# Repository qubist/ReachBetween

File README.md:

RB02
====

Simple, cheap, hackable, DIY, open-source USB-C input switcher

Background
----------

I couldn't find a good USB-C switch with two outputs that wasn't hundreds of
dollars, so I built my own. (Also I wanted an excuse to learn PCB design, and I
was able to secure a few free sample rotary switches from an electronics
company.) The result is the RB02, a two-output one-input bidirectional USB-C
input switcher smaller than a credit card.

The RB02 has three USB-C ports, one on the front and two on the back. A knob on top has three positions, left, right, and center. In the left or right position, the device connects the USB port on the front to the left or right USB port on the back. 

It's resonable to make as a weekend project as long as you've got a fine
soldering iron for the few surface-mount pads.

Gallery
-------

FIXME

Bill of Materials
-----------------

| Item                                              | Manufacturer  | Part number      | Quantity | Unit price | Total price              |
|---------------------------------------------------|---------------|------------------|----------|------------|--------------------------|
| Rotary switch                                     | NKK Switches  | MRA-403-A        | 1        | $24.17     | $24.17                   |
| 18-8 Stainless Steel Socket Head Screw, M2 x 25mm | McMaster Carr | 91292A032        | 4        |            | $6.21 (pack of 10)       |
| 18-8 Stainless Steel Hex Nut, M2                  | McMaster Carr | 91828A111        | 4        |            | $6.14 (pack of 100)      |
| 1/4" Adhesive-Back Bumper                         | McMaster Carr | 8215K219         | 3        | $2.06      | $6.18                    |
| Custom Printed Circuit Board                      | Aisler        |                  | 1        | $7.04      | $21.10 (minimum order 3) |
| Standard LED                                      |               |                  | 1        |            |                          |
| Standard resistor                                 |               |                  | 1        |            |                          |
| USB-C receptacle                                  | JAE           | DX07S016JA1R1500 | 3        | $1.67      | $5.01                    |
|                                                   |               |                  |          |            | **~$70**                 |

Assembly
--------

### PCB assembly

FIXME

- Different resistor values result in different brightnesses of the LED. 420Ω
  is around full brightness. I like mine pretty dim so I chose FIXMEΩ
- To disable the LED entirely just remove the resistor. Or don't install the
  LED at all. One could easily redesign the case to remove the LED hole.

### Case assembly

FIXME

- Clip off leads sticking through PCB to 2mm or less
- MR-A403 should be installed in this configuration from top to bottom:
  * Knob
  * Hex Face Nut
  * Case
  * Locking Ring (with nub pointing up into hole in case)
  * Factory Assembled switch
  Refer to page 4 of the [datasheet](for definitions and details).

License
-------

[GNU General Public License v3.0](LICENSE)

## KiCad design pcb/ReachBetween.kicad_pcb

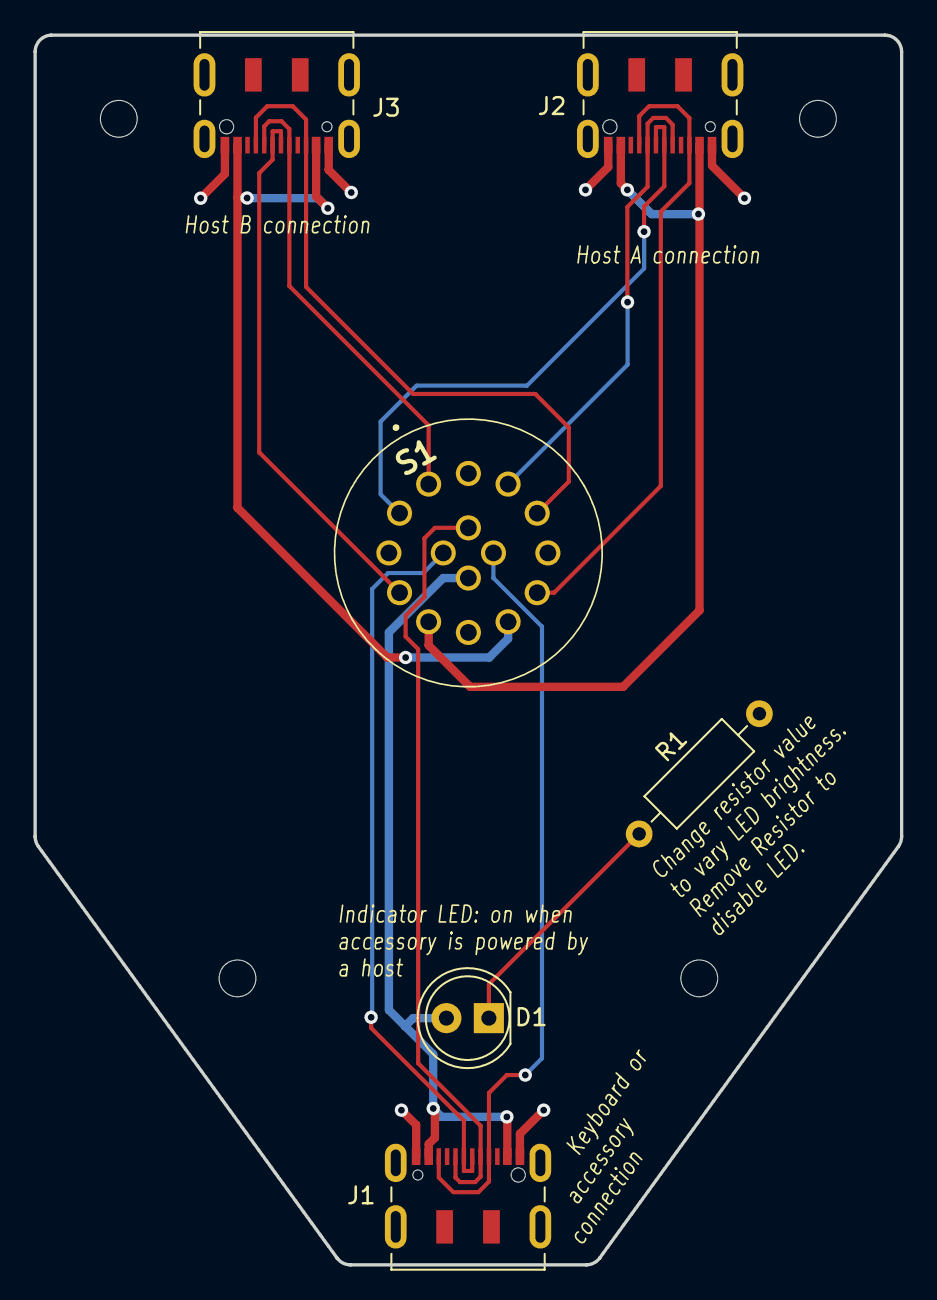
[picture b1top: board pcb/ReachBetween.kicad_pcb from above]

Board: 2 copper layers, 51.8 x 73.5 mm, 6 parts (0 on the bottom side), 14 nets.

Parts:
D1: LED; LED_D5.0mm_Clear
J1: IN; USB_C_Receptacle_JAE_DX07S016JA1R1500_AislerCompatible
J2: Out A; USB_C_Receptacle_JAE_DX07S016JA1R1500_AislerCompatible
J3: Out B; USB_C_Receptacle_JAE_DX07S016JA1R1500_AislerCompatible
R1: 5.1K; R_Axial_DIN0207_L6.3mm_D2.5mm_P10.16mm_Horizontal
S1: MRA403; Rotary_Switch_NKK_MRA403-BB_2-3

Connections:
/CC A: J2.A5 (CC1), J2.B5 (CC2), S1.6
/CC B: J3.A5 (CC1), J3.B5 (CC2), S1.4
/CC in: J1.A5 (CC1), J1.B5 (CC2), S1.D1 (COM_3)
/Common Ground: J1.A1 (GND), J1.A12 (GND), J1.B1 (GND), J1.B12 (GND), J1.S1 (SHIELD), J2.A1 (GND), J2.A12 (GND), J2.B1 (GND), J2.B12 (GND), J2.S1 (SHIELD), J3.A1 (GND), J3.A12 (GND), J3.B1 (GND), J3.B12 (GND), J3.S1 (SHIELD), R1.2
/D+ A: J2.A6 (D+), J2.B6 (D+), S1.12
/D+ B: J3.A6 (D+), J3.B6 (D+), S1.10
/D+ in: J1.A6 (D+), J1.B6 (D+), S1.C1 (COM_3)
/D- A: J2.A7 (D-), J2.B7 (D-), S1.3
/D- B: J3.A7 (D-), J3.B7 (D-), S1.1
/D- in: J1.A7 (D-), J1.B7 (D-), S1.B1 (COM_2)
/VBUS A: J2.A4 (VBUS), J2.A9 (VBUS), J2.B4 (VBUS), J2.B9 (VBUS), S1.9
/VBUS B: J3.A4 (VBUS), J3.A9 (VBUS), J3.B4 (VBUS), J3.B9 (VBUS), S1.7
/VBUS in: D1.2 (A), J1.A4 (VBUS), J1.A9 (VBUS), J1.B4 (VBUS), J1.B9 (VBUS), S1.A1 (COM_1)
unnamed: D1.1 (K), R1.1

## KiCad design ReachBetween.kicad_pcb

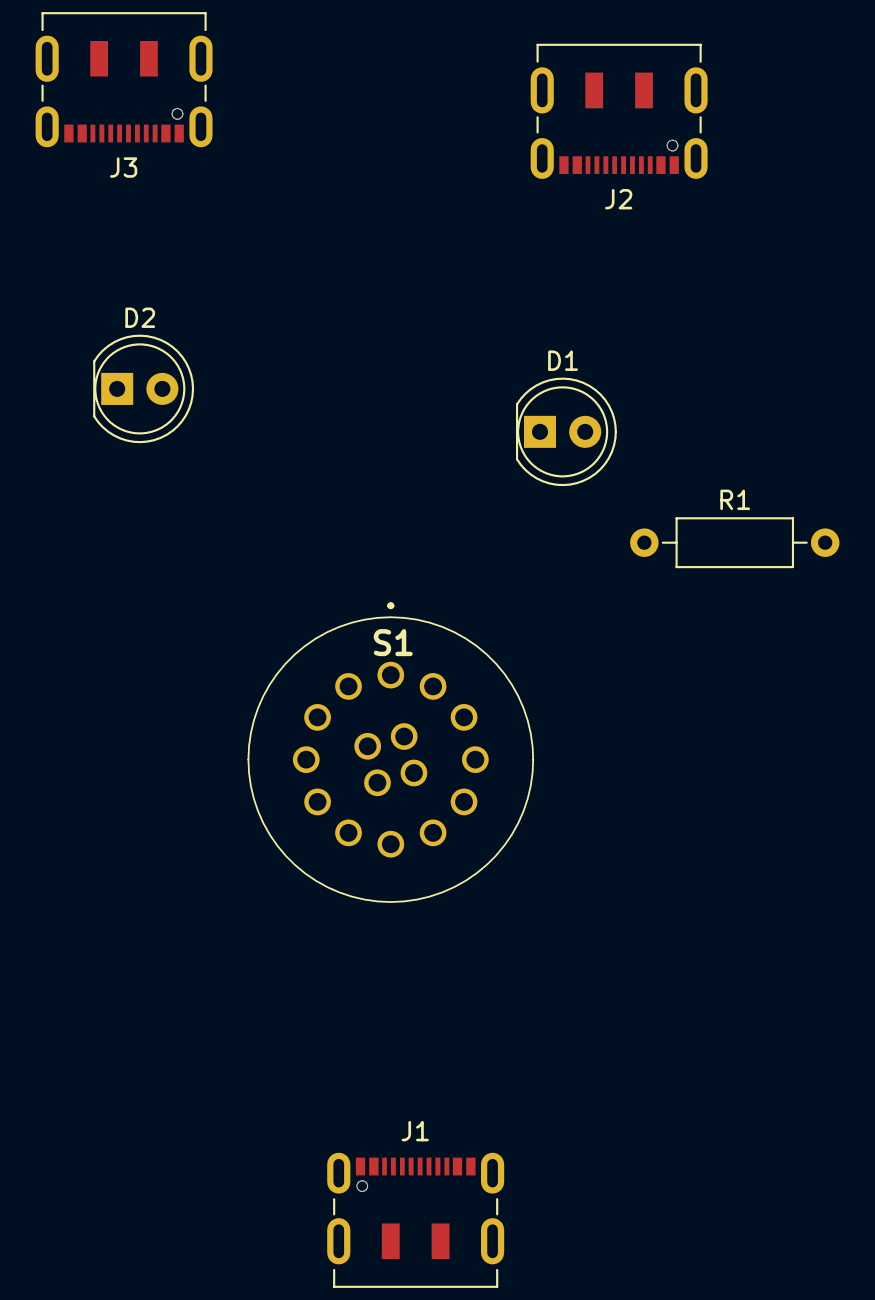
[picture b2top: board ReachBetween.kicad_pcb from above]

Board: 2 copper layers, 7 parts (0 on the bottom side), 14 nets, no tracks yet.

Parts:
D1, D2: LED; LED_D5.0mm_Clear
J1, J2, J3: USB_C_Receptacle_USB2.0; USB_C_Receptacle_JAE_DX07S016JA1R1500
R1: 470; R_Axial_DIN0207_L6.3mm_D2.5mm_P10.16mm_Horizontal
S1: MRA403; Rotary_Switch_NKK_MRA403-BB_2-3

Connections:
unnamed: D1.1 (K), D2.1 (K), R1.2
unnamed: J1.A1 (GND), J1.A12 (GND), J1.B1 (GND), J1.B12 (GND), J2.A1 (GND), J2.A12 (GND), J2.B1 (GND), J2.B12 (GND), J3.A1 (GND), J3.A12 (GND), J3.B1 (GND), J3.B12 (GND), R1.1
unnamed: J1.A4 (VBUS), J1.A9 (VBUS), J1.B4 (VBUS), J1.B9 (VBUS), S1.A1 (COM_1)
unnamed: J1.A5 (CC1), J1.B5 (CC2), S1.D1 (COM_3)
unnamed: J1.A6 (D+), J1.B6 (D+), S1.C1 (COM_3)
unnamed: J1.A7 (D-), J1.B7 (D-), S1.B1 (COM_2)
unnamed: D1.2 (A), J2.A4 (VBUS), J2.A9 (VBUS), J2.B4 (VBUS), J2.B9 (VBUS), S1.7
unnamed: J2.A5 (CC1), J2.B5 (CC2), S1.4
unnamed: J2.A6 (D+), J2.B6 (D+), S1.10
unnamed: J2.A7 (D-), J2.B7 (D-), S1.1
unnamed: D2.2 (A), J3.A4 (VBUS), J3.A9 (VBUS), J3.B4 (VBUS), J3.B9 (VBUS), S1.9
unnamed: J3.A5 (CC1), J3.B5 (CC2), S1.6
unnamed: J3.A6 (D+), J3.B6 (D+), S1.12
unnamed: J3.A7 (D-), J3.B7 (D-), S1.3

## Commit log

2022-03-31 Create LICENSE
2022-04-20 Finish board
2022-04-21 Fix warnings (unconnected tracks)!
2022-04-21 Round tracks
2022-04-21 Teardrop tracks
2022-04-21 Update version number
2022-04-21 Update version number correspondingly on source PCB
2022-04-21 Round silkscreen lines on back
2022-04-25 Rearrange
2022-04-25 Add case design files
2022-05-06 Update case after seeing boards in person

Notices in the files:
pcb/ReachBetween.kicad_pcb:
© Will Harris-Braun
CC BY-SA 3.0
